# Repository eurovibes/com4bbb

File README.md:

<!-- SPDX-FileCopyrightText: 2021 Benedikt Spranger <b.spranger@linutronix.de> -->
<!-- SPDX-License-Identifier: CERN-OHL-S-2.0 -->

# com4bbb - A RS485 / WiFi cape for Beaglebone Black

The Beaglobone Black is a TI Sitara AM3359 ARM Cortex-A8 CPU based
evaluation board with two 40pin 100mil pinsockets. These pinsockets
can be used for additional functionality boards called capes.
The com4bbb cape enhance the Beaglebone Black by a ESP32 based WiFi module
and a RS485 tranceiver.

## License rules

com4bbb is provided under the terms of the CERN-OHL-S license version 2 as
provided in the LICENSES/CERN-OHL-S-2.0 file.

Instead of adding license boilerplates to the individual files, com4bbb uses
SPDX license identifiers, which are machine parseable and considered legaly
equivalent.

The SPDX license identifier in com4bbb shall be added at the first possible
line in a file which can contain a comment. This is normally the first line
except for scripts. Scripts require the #!PATH_TO_INTERPRETER tag in the
first line; place the SPDX identifier into the second line.

The SPDX license identifier is added in form of a comment.

## Copyright and License

Copyright Benedikt Spranger 2021.
This source describes Open Hardware and is licensed under the CERNOHL-S v2.
You may redistribute and modify this source and make products using it
under the terms of the CERN-OHL-S v2
(https://ohwr.org/cern ohl s v2.txt ).
This source is distributed WITHOUT ANY EXPRESS OR IMPLIED
WARRANTY, INCLUDING OF MERCHANTABILITY, SATISFACTORY
QUALITY AND FITNESS FOR A PARTICULAR PURPOSE. Please see
the CERN-OHL-S v2 for applicable conditions.
Source location: https://github.com/eurovibes/com4bbb
As per CERN-OHL-S v2 section 4, should You produce hardware based
on this source, You must where practicable maintain the Source Location
visible on the external case of the com4bbb or other products you make using
this source.

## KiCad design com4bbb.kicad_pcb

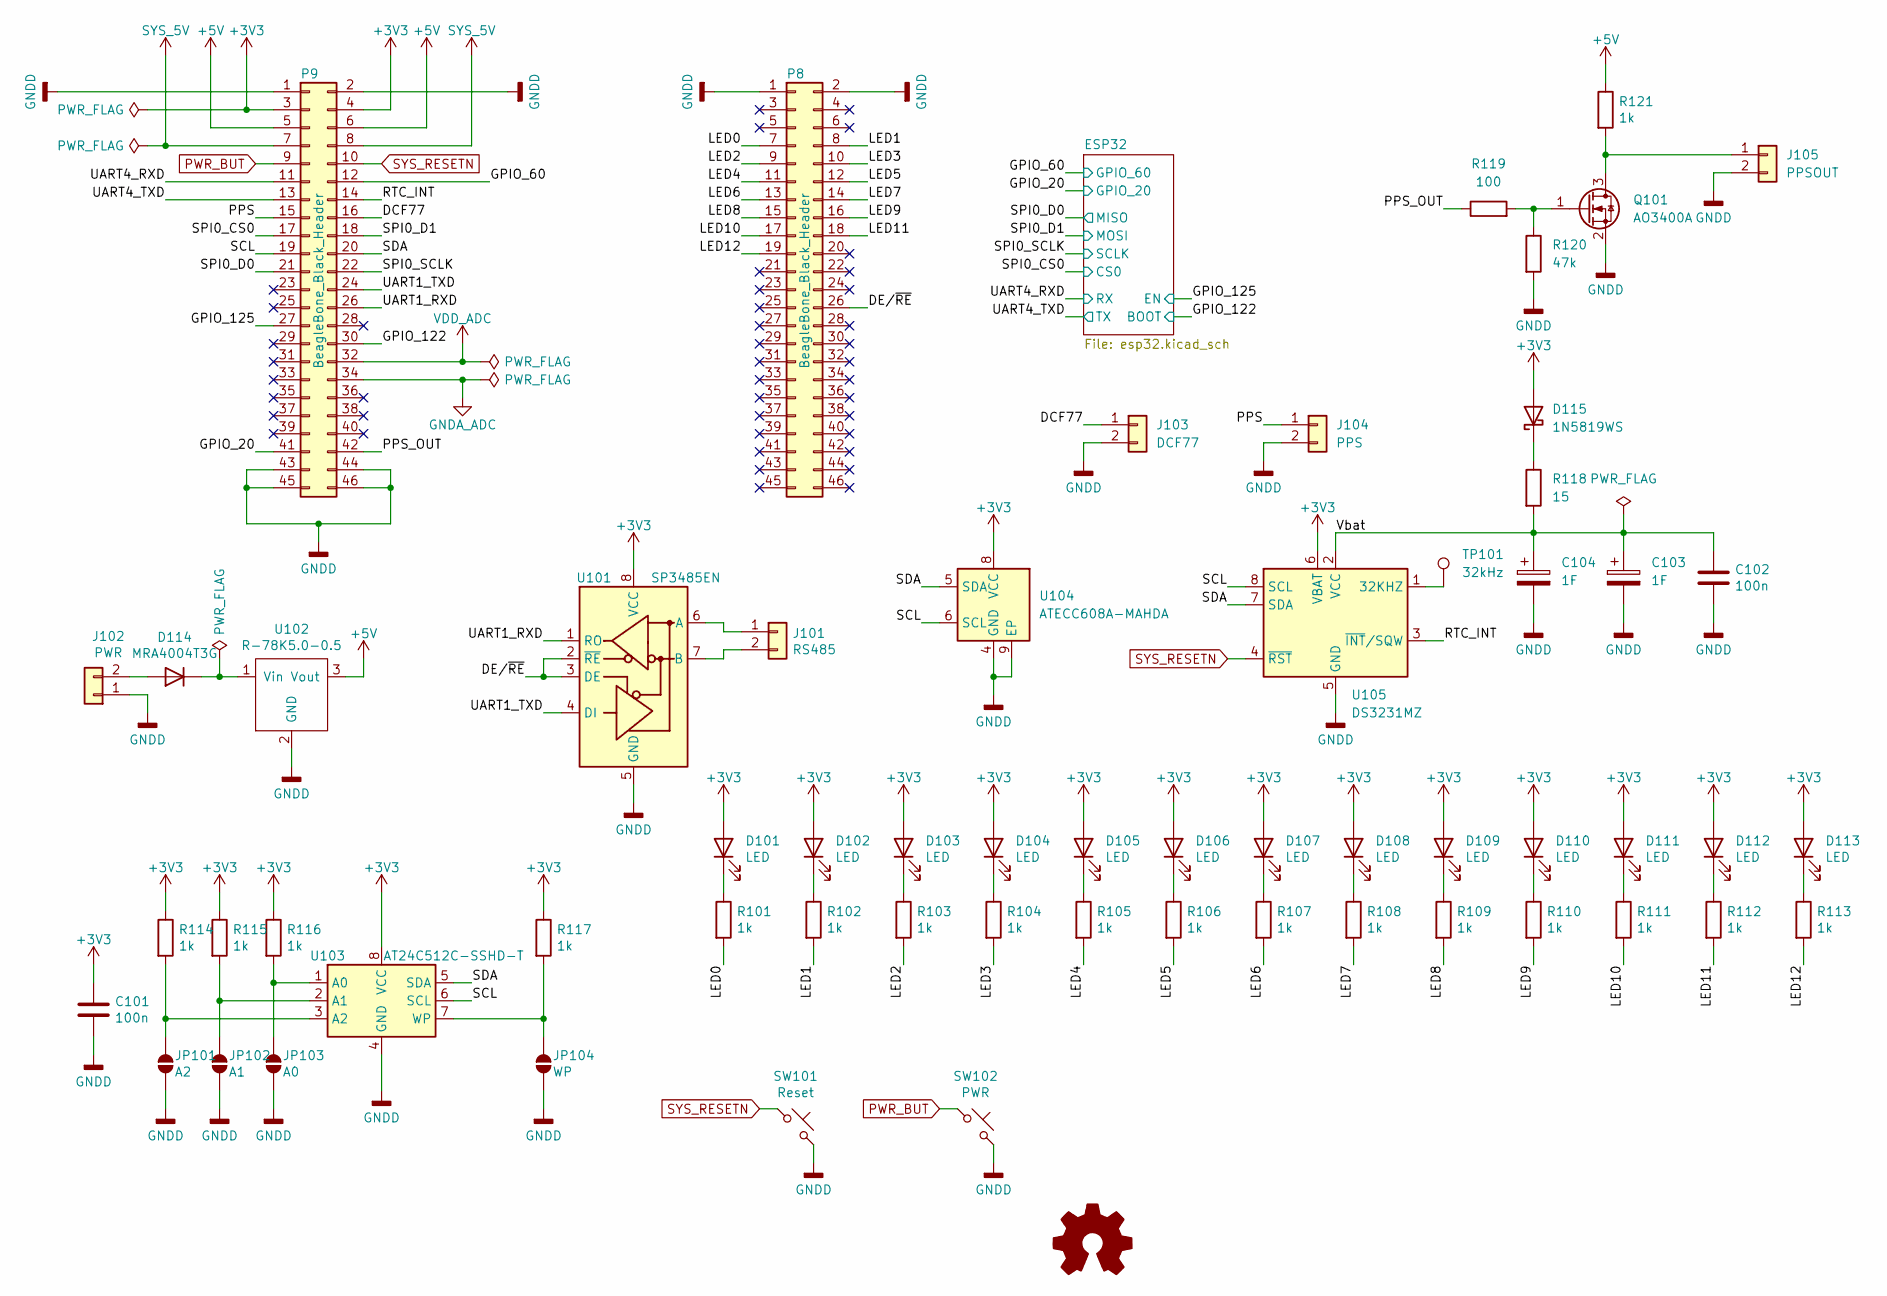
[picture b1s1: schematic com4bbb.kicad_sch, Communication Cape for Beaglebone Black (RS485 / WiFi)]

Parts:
C101, C102: 100n; C_0402_1005Metric; lcsc# C1525
C103, C104: 1F; CP_Radial_D8.0mm_P3.50mm
D101, D102, D103, D104, D105, D106, D107, D108, D109, D110, D111, D112, D113: LED; LED_0603_1608Metric; lcsc# C2286
D114: MRA4004T3G; D_SMA; lcsc# C40324
D115: 1N5819WS; D_SOD-323; lcsc# C191023
J101: RS485; TerminalBlock_WAGO_236-402_1x02_P5.00mm_45Degree; digikey# 2946-236-402-ND
J102: PWR; TerminalBlock_WAGO_236-402_1x02_P5.00mm_45Degree; digikey# 2946-236-402-ND
J103: DCF77; PinHeader_1x02_P2.54mm_Vertical
J104: PPS; PinHeader_1x02_P2.54mm_Vertical
J105: PPSOUT; PinHeader_1x02_P2.54mm_Vertical
JP101: A2; SolderJumper-2_P1.3mm_Open_RoundedPad1.0x1.5mm
JP102: A1; SolderJumper-2_P1.3mm_Open_RoundedPad1.0x1.5mm
JP103: A0; SolderJumper-2_P1.3mm_Open_RoundedPad1.0x1.5mm
JP104: WP; SolderJumper-2_P1.3mm_Open_RoundedPad1.0x1.5mm
P8, P9: BeagleBone_Black_Header; PinHeader_2x23_P2.54mm_Vertical
Q101: AO3400A; SOT-23
R101, R102, R103, R104, R105, R106, R107, R108, R109, R110, R111, R112, R113, R114, R115, R116, R117, R121: 1k; R_0402_1005Metric; lcsc# C11702
R118: 15; R_0805_2012Metric; lcsc# C17480
R119: 100; R_0402_1005Metric
R120: 47k; R_0402_1005Metric
SW101: Reset; SW_PUSH_6mm
SW102: PWR; SW_PUSH_6mm
TP101: 32kHz; TestPoint_Pad_1.0x1.0mm
U101: SP3485EN; SOIC-8_3.9x4.9mm_P1.27mm; lcsc# C8963
U102: R-78K5.0-0.5; WPMDH1100xx1S
U103: AT24C512C-SSHD-T; SOIC-8_3.9x4.9mm_P1.27mm; lcsc# C6482
U104: ATECC608A-MAHDA; DFN-8-1EP_3x2mm_P0.5mm_EP1.3x1.5mm; lcsc# C17561150
U105: DS3231MZ; SOIC-8_3.9x4.9mm_P1.27mm; lcsc# C107410

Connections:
+3V3: C101.1, D101.2 (A), D102.2 (A), D103.2 (A), D104.2 (A), D105.2 (A), D106.2 (A), D107.2 (A), D108.2 (A), D109.2 (A), D110.2 (A), D111.2 (A), D112.2 (A), D113.2 (A), D115.2 (A), P9.3, P9.4, R114.1, R115.1, R116.1, R117.1, U101.8 (VCC), U103.8 (VCC), U104.8 (VCC), U105.6 (VBAT); also elsewhere on the board
+5V: P9.5, P9.6, R121.1, U102.3 (Vout)
/DCF77: J103.1, P9.16
/DE/~RE: P8.26, U101.2 (~RE), U101.3 (DE)
/GPIO_20: P9.41; also elsewhere on the board
/GPIO_60: P9.12; also elsewhere on the board
/GPIO_122: P9.30; also elsewhere on the board
/GPIO_125: P9.27; also elsewhere on the board
/LED0: P8.7, R101.2
/LED1: P8.8, R102.2
/LED2: P8.9, R103.2
/LED3: P8.10, R104.2
/LED4: P8.11, R105.2
/LED5: P8.12, R106.2
/LED6: P8.13, R107.2
/LED7: P8.14, R108.2
/LED8: P8.15, R109.2
/LED9: P8.16, R110.2
/LED10: P8.17, R111.2
/LED11: P8.18, R112.2
/LED12: P8.19, R113.2
/PPS: J104.1, P9.15
/PPS_OUT: P9.42, R119.1
/RTC_INT: P9.14, U105.3 (~INT/SQW)
/SCL: P9.19, U103.6 (SCL), U104.6 (SCL), U105.8 (SCL)
/SDA: P9.20, U103.5 (SDA), U104.5 (SDA), U105.7 (SDA)
/SPI0_CS0: P9.17; also elsewhere on the board
/SPI0_D0: P9.21; also elsewhere on the board
/SPI0_D1: P9.18; also elsewhere on the board
/SPI0_SCLK: P9.22; also elsewhere on the board
/UART1_RXD: P9.26, U101.1 (RO)
/UART1_TXD: P9.24, U101.4 (DI)
/UART4_RXD: P9.11; also elsewhere on the board
/UART4_TXD: P9.13; also elsewhere on the board
/Vbat: C102.1, C103.1, C104.1, R118.2, U105.2 (VCC)
GNDA_ADC: P9.34
GNDD: C101.2, C102.2, C103.2, C104.2, J102.1, J103.2, J104.2, J105.2, JP101.2 (B), JP102.2 (B), JP103.2 (B), JP104.2 (B), P8.1, P8.2, P9.1, P9.2, P9.43, P9.44, P9.45, P9.46, Q101.2 (S), R120.2, SW101.2, SW102.2, U101.5 (GND), U102.2 (GND), U103.4 (GND), U104.4 (GND), U104.9 (EP), U105.5 (GND); also elsewhere on the board
unnamed: D101.1 (K), R101.1
unnamed: D102.1 (K), R102.1
unnamed: D103.1 (K), R103.1
unnamed: D104.1 (K), R104.1
unnamed: D105.1 (K), R105.1
unnamed: D106.1 (K), R106.1
unnamed: D107.1 (K), R107.1
unnamed: D108.1 (K), R108.1
unnamed: D109.1 (K), R109.1
unnamed: D110.1 (K), R110.1
unnamed: D111.1 (K), R111.1
unnamed: D112.1 (K), R112.1
unnamed: D113.1 (K), R113.1
unnamed: D114.2 (A), J102.2
unnamed: D114.1 (K), U102.1 (Vin)
unnamed: D115.1 (K), R118.1
unnamed: J101.1, U101.6 (A)
unnamed: J101.2, U101.7 (B)
unnamed: J105.1, Q101.3 (D), R121.2
unnamed: JP101.1 (A), R114.2, U103.3 (A2)
unnamed: JP102.1 (A), R115.2, U103.2 (A1)
unnamed: JP103.1 (A), R116.2, U103.1 (A0)
unnamed: JP104.1 (A), R117.2, U103.7 (WP)
unnamed: Q101.1 (G), R119.2, R120.1
unnamed: TP101.1, U105.1 (32KHZ)
PWR_BUT: P9.9, SW102.1
SYS_5V: P9.7, P9.8
SYS_RESETN: P9.10, SW101.1, U105.4 (~RST)
VDD_ADC: P9.32

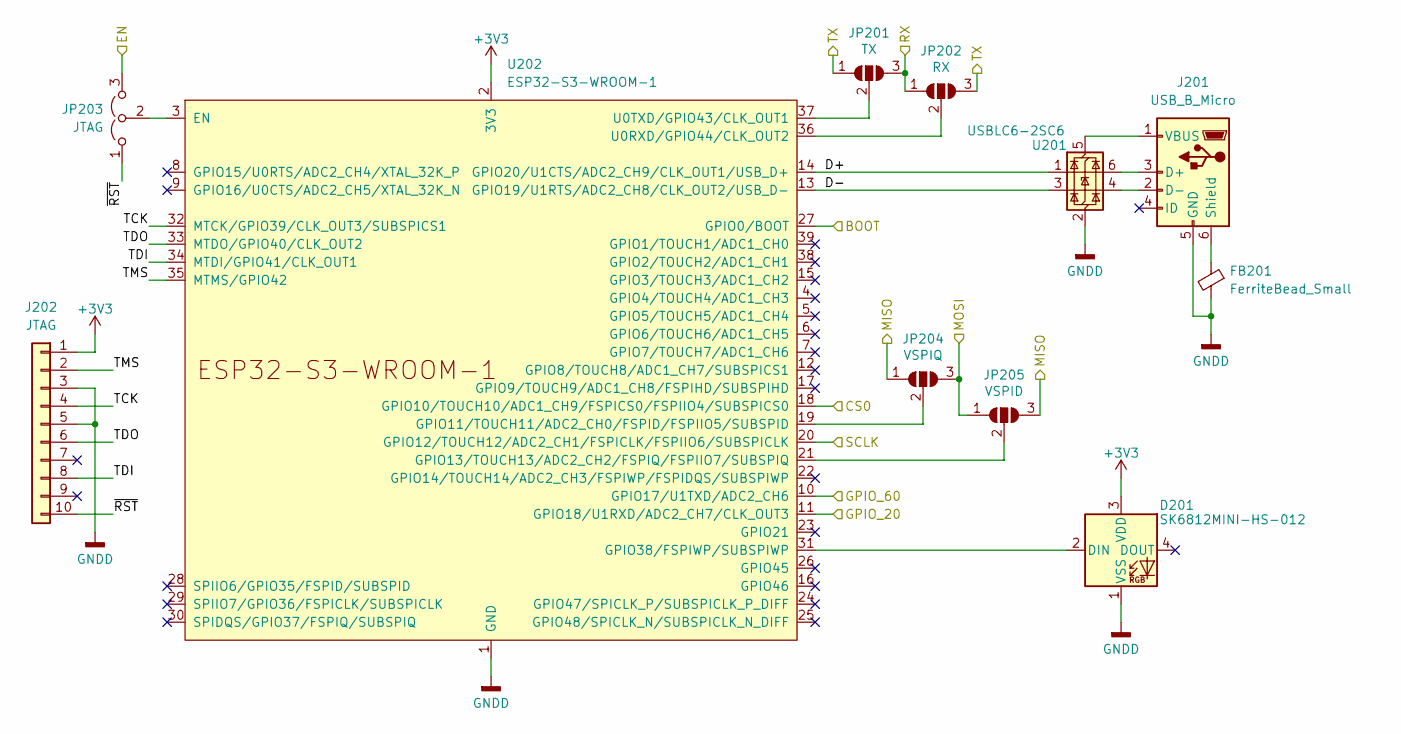
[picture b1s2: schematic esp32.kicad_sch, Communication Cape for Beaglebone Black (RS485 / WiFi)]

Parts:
D201: SK6812MINI-HS-012; LED_WS2812B-Mini_PLCC4_3.5x3.5mm; lcsc# C2922787
FB201: FerriteBead_Small; L_0402_1005Metric; lcsc# C14709
J201: USB_B_Micro; USB_Micro-B_Amphenol_10103594-0001LF_Horizontal; lcsc# C428495
J202: JTAG; Tag-Connect_TC2050-IDC-FP_2x05_P1.27mm_Vertical
JP201: TX; SolderJumper-3_P1.3mm_Open_RoundedPad1.0x1.5mm
JP202: RX; SolderJumper-3_P1.3mm_Open_RoundedPad1.0x1.5mm
JP203: JTAG; PinHeader_1x03_P2.54mm_Vertical
JP204: VSPIQ; SolderJumper-3_P1.3mm_Open_RoundedPad1.0x1.5mm
JP205: VSPID; SolderJumper-3_P1.3mm_Open_RoundedPad1.0x1.5mm
U201: USBLC6-2SC6; SOT-23-6; lcsc# C2687116
U202: ESP32-S3-WROOM-1; ESP32-S3-WROOM-1U; lcsc# C3013946

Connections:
+3V3: D201.3 (VDD), J202.1, U202.2 (3V3); also elsewhere on the board
/ESP32/D+: U201.1 (I/O1), U202.14 (GPIO20/U1CTS/ADC2_CH9/CLK_OUT1/USB_D+)
/ESP32/D-: U201.3 (I/O2), U202.13 (GPIO19/U1RTS/ADC2_CH8/CLK_OUT2/USB_D-)
/ESP32/TCK: J202.4, U202.32 (MTCK/GPIO39/CLK_OUT3/SUBSPICS1)
/ESP32/TDI: J202.8, U202.34 (MTDI/GPIO41/CLK_OUT1)
/ESP32/TDO: J202.6, U202.33 (MTDO/GPIO40/CLK_OUT2)
/ESP32/TMS: J202.2, U202.35 (MTMS/GPIO42)
/ESP32/~RST: J202.10, JP203.1 (A)
/GPIO_20: U202.11 (GPIO18/U1RXD/ADC2_CH7/CLK_OUT3); also elsewhere on the board
/GPIO_60: U202.10 (GPIO17/U1TXD/ADC2_CH6); also elsewhere on the board
/GPIO_122: U202.27 (GPIO0/BOOT); also elsewhere on the board
/GPIO_125: JP203.3 (B); also elsewhere on the board
/SPI0_CS0: U202.18 (GPIO10/TOUCH10/ADC1_CH9/FSPICS0/FSPIIO4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); also elsewhere on the board
/SPI0_D0: JP204.1 (A), JP205.3 (B); also elsewhere on the board
/SPI0_D1: JP204.3 (B), JP205.1 (A); also elsewhere on the board
/SPI0_SCLK: U202.20 (GPIO12/TOUCH12/ADC2_CH1/FSPICLK/FSPIIO6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); also elsewhere on the board
/UART4_RXD: JP201.3 (B), JP202.1 (A); also elsewhere on the board
/UART4_TXD: JP201.1 (A), JP202.3 (B); also elsewhere on the board
GNDD: D201.1 (VSS), FB201.2, J201.5 (GND), J202.3, J202.5, U201.2 (GND), U202.1 (GND), U202.40 (GND), U202.41 (GND); also elsewhere on the board
unnamed: D201.2 (DIN), U202.31 (GPIO38/FSPIWP/SUBSPIWP)
unnamed: J201.3 (D+), U201.6 (I/O1)
unnamed: J201.2 (D-), U201.4 (I/O2)
unnamed: FB201.1, J201.6 (Shield)
unnamed: J201.1 (VBUS), U201.5 (VBUS)
unnamed: JP201.2 (C), U202.37 (U0TXD/GPIO43/CLK_OUT1)
unnamed: JP202.2 (C), U202.36 (U0RXD/GPIO44/CLK_OUT2)
unnamed: JP203.2 (C), U202.3 (EN)
unnamed: JP204.2 (C), U202.19 (GPIO11/TOUCH11/ADC2_CH0/FSPID/FSPIIO5/S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)
unnamed: JP205.2 (C), U202.21 (GPIO13/TOUCH13/ADC2_CH2/FSPIQ/FSPIIO7/S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)

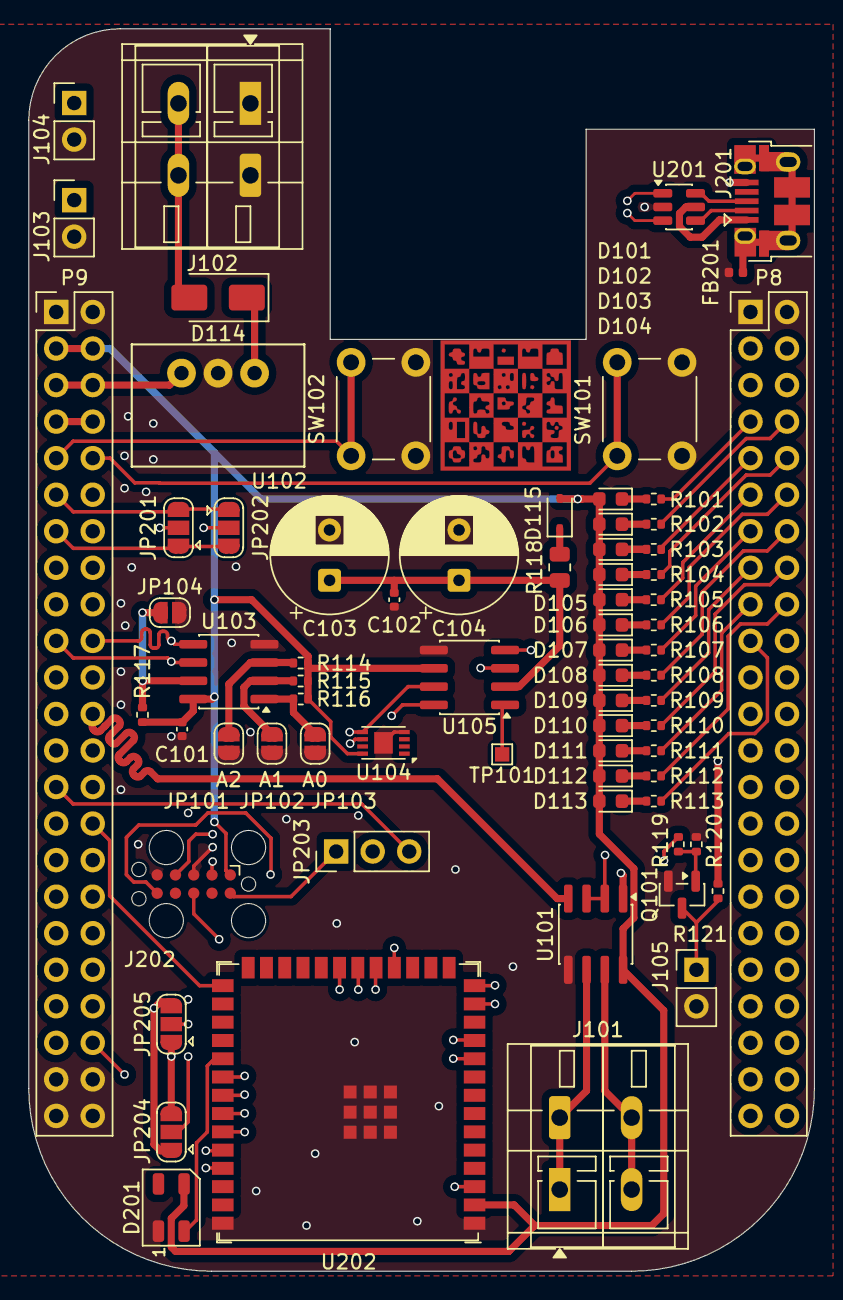
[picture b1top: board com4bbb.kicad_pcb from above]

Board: 4 copper layers, 54.6 x 86.4 mm, 71 parts (0 on the bottom side), 81 nets.

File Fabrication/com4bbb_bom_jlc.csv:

"Comment","Designator","Footprint","LCSC Part #"
"100n","C101,C102","C_0402_1005Metric","C1525"
"1N5819WS","D115","D_SOD-323","C191023"
"LED","D101,D102,D103,D104,D105,D106,D107,D108,D109,D110,D111,D112,D113","LED_0603_1608Metric","C2286"
"MRA4004T3G","D114","D_SMA","C40324"
"SK6812MINI","D201","LED_SK6812MINI_PLCC4_3.5x3.5mm_P1.75mm","C2922787"
"FerriteBead_Small","FB201","L_0402_1005Metric","C14709"
"USB_B_Micro","J201","USB_Micro-B_Amphenol_10103594-0001LF_Horizontal","C428495"
"15","R118","R_0805_2012Metric","C17480"
"1k","R101,R102,R103,R104,R105,R106,R107,R108,R109,R110,R111,R112,R113,R114,R115,R116,R117,R121","R_0402_1005Metric","C11702"
"AT24C512C-SSHD-T","U103","SOIC-8_3.9x4.9mm_P1.27mm","C6482"
"ATECC608A-MAHDA","U104","DFN-8-1EP_3x2mm_P0.5mm_EP1.3x1.5mm","C17561150"
"DS3231MZ","U105","SOIC-8_3.9x4.9mm_P1.27mm","C107410"
"ESP32-S3-WROOM-1","U202","ESP32-S3-WROOM-1U","C3013946"
"SP3485EN","U101","SOIC-8_3.9x4.9mm_P1.27mm","C8963"
"USBLC6-2SC6","U201","SOT-23-6","C2687116"

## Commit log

2021-06-14 Initial
2021-06-14 Order v0.1
2021-06-14 Add github workflow
2021-06-14 com4bbb: A RS485 / WiFi cape for the Beaglebone Black
    The Beaglobone Black is a TI Sitara AM3359 ARM Cortex-A8 CPU based
    evaluation board with two 40pin 100mil pinsockets. These pinsockets
    can be used for additional functionality boards called capes.
    The com4bbb cape enhance the Beaglebone Black by a ESP32 based WiFi module
    and a RS485 tranceiver.
    Initial commit.
2021-06-14 Add KiPlot configuration
    KiPlot is a KiCAD automatisation suite to generate Gerber files or generate
    a PDF from the schematic file.
    Add a KiPlot configuration to generate Gerber and schematic PDFs.
2021-06-14 Add github workflow
    Use a github workflow to automaticaly call KiPlot to generate a base
    board documentation.
2021-06-15 Add open hardware logo
    Change license to CERN-OHL-S v2, which can be found at
    https://ohwr.org/cern_ohl_s_v2.txt
2021-06-15 Add a logo
    Every project should have a logo. Add one.
2021-06-16 Initial gh page
    Add gh pages for project documentation.
2021-06-16 Rework github workflow
    Instead open coding the KiBot calls use the github workflow macros
    provided by INTI-CMNB.
2021-06-16 Publish generated documentation
    The github actions generate a bunch of documentation. Publish them on
    github pages.
2021-06-16 Deploying to gh-pages from @ eurovibes/com4bbb@9685f37fe73d0f9fecb9bcfe8c765d7dcbed1d69 🚀
2021-06-27 Connect missing boot pin
    The ESP32-wroom-32u module use IO0 to enter boot mode. In boot mode
    the device can be flashed. Connect IO0 to the Beagle Bone to be able
    to update firmware on demand.
2021-06-27 Deploying to gh-pages from @ eurovibes/com4bbb@f9881c3c0cdcbf8602448e5e20b1d4b7fe78fb2b 🚀
2021-06-27 Deploying to gh-pages from @ eurovibes/com4bbb@293a328ee0af4224feb225cef8fda064ee550dd6 🚀
2025-11-14 Update to KiCAD version 9
2025-11-14 Convert symbol libraries to new KiCAD library format
2025-11-14 Move footprints into separate directory
2025-11-14 Change to stable KiBot action v2_k9
2025-11-14 Add Espressif symbol library
2025-11-17 Deploying to gh-pages from @ eurovibes/com4bbb@82d1824c6370e45de1223c278c0f35fdd320c161 🚀
2025-11-20 Deploying to gh-pages from @ eurovibes/com4bbb@95f4e9637be254ab0389a526c06286599a028323 🚀
2025-11-20 Deploying to gh-pages from @ eurovibes/com4bbb@d3eac2ac1b31b15b7d5a78c3437cb80c41fe706d 🚀
2025-11-20 Deploying to gh-pages from @ eurovibes/com4bbb@15e52f9b91c3b467cbe6f6bf240b6c0b15303a34 🚀
2025-11-20 Move gerber zip archive into download directory
2025-11-20 Deploying to gh-pages from @ eurovibes/com4bbb@703e94b3b70e2b39cedc4a1287db2450ea9a1f9e 🚀
2025-11-20 Add License badge
2025-11-20 Generate BOMs for FusionPCB and JLCPCB
2025-11-20 Add version badge
2025-11-20 Deploying to gh-pages from @ eurovibes/com4bbb@8c1bc7cfa87728f9fa315841c1321edc5f412c9f 🚀
2025-11-20 Deploying to gh-pages from @ eurovibes/com4bbb@b88d3350758cdd2fa0de41303670df8c3ff89991 🚀
2025-11-21 Deploying to gh-pages from @ eurovibes/com4bbb@1679398a5a587527b1874f380ab776cea805480a 🚀
2025-11-21 Rework order information
2025-11-21 Update to ESP32-S3-WROOM-1U
2025-11-21 Deploying to gh-pages from @ eurovibes/com4bbb@42d69c2a306533c8d229c390ccab635be9608f96 🚀
2025-11-22 Add RTC and secure memory
2025-11-22 Deploying to gh-pages from @ eurovibes/com4bbb@4d958de001089e8659ce9f94b155ed1b126b3772 🚀
2025-11-22 Change jumper position
2025-11-22 Deploying to gh-pages from @ eurovibes/com4bbb@a90238877db731615032046896abdac1a6abb7a0 🚀
2025-11-29 Rework PCB page settings
2025-11-29 Add DCF77 clock input
2025-11-29 Add PPS input
2025-11-29 Bump to 0.2
2025-11-29 Deploying to gh-pages from @ eurovibes/com4bbb@739ffe855d2b3574c29f554fab249f77e0e9397e 🚀
2025-12-05 Add PPS output
2025-12-05 Deploying to gh-pages from @ eurovibes/com4bbb@b2e51206528f1b6ae8ac0e6dcaabf5c8ee8544cf 🚀
2025-12-07 Fix SK6812 footprint mess
2025-12-07 Deploying to gh-pages from @ eurovibes/com4bbb@ad5f9b1a2a3626d344ceb5e74cdc26189343dac5 🚀

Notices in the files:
com4bbb.kicad_pcb:
This work is licensed under the CERN-OHL-S v2
